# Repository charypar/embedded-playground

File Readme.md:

# Niche device firmware

## Flashing bootloader

Using a probe

```sh
make flash-bootloader
```

## Flashing firmware

For Spinny, for example:

With a probe:

```sh
make flash-spinny
```

Over USB

```sh
make upload-spinny
```

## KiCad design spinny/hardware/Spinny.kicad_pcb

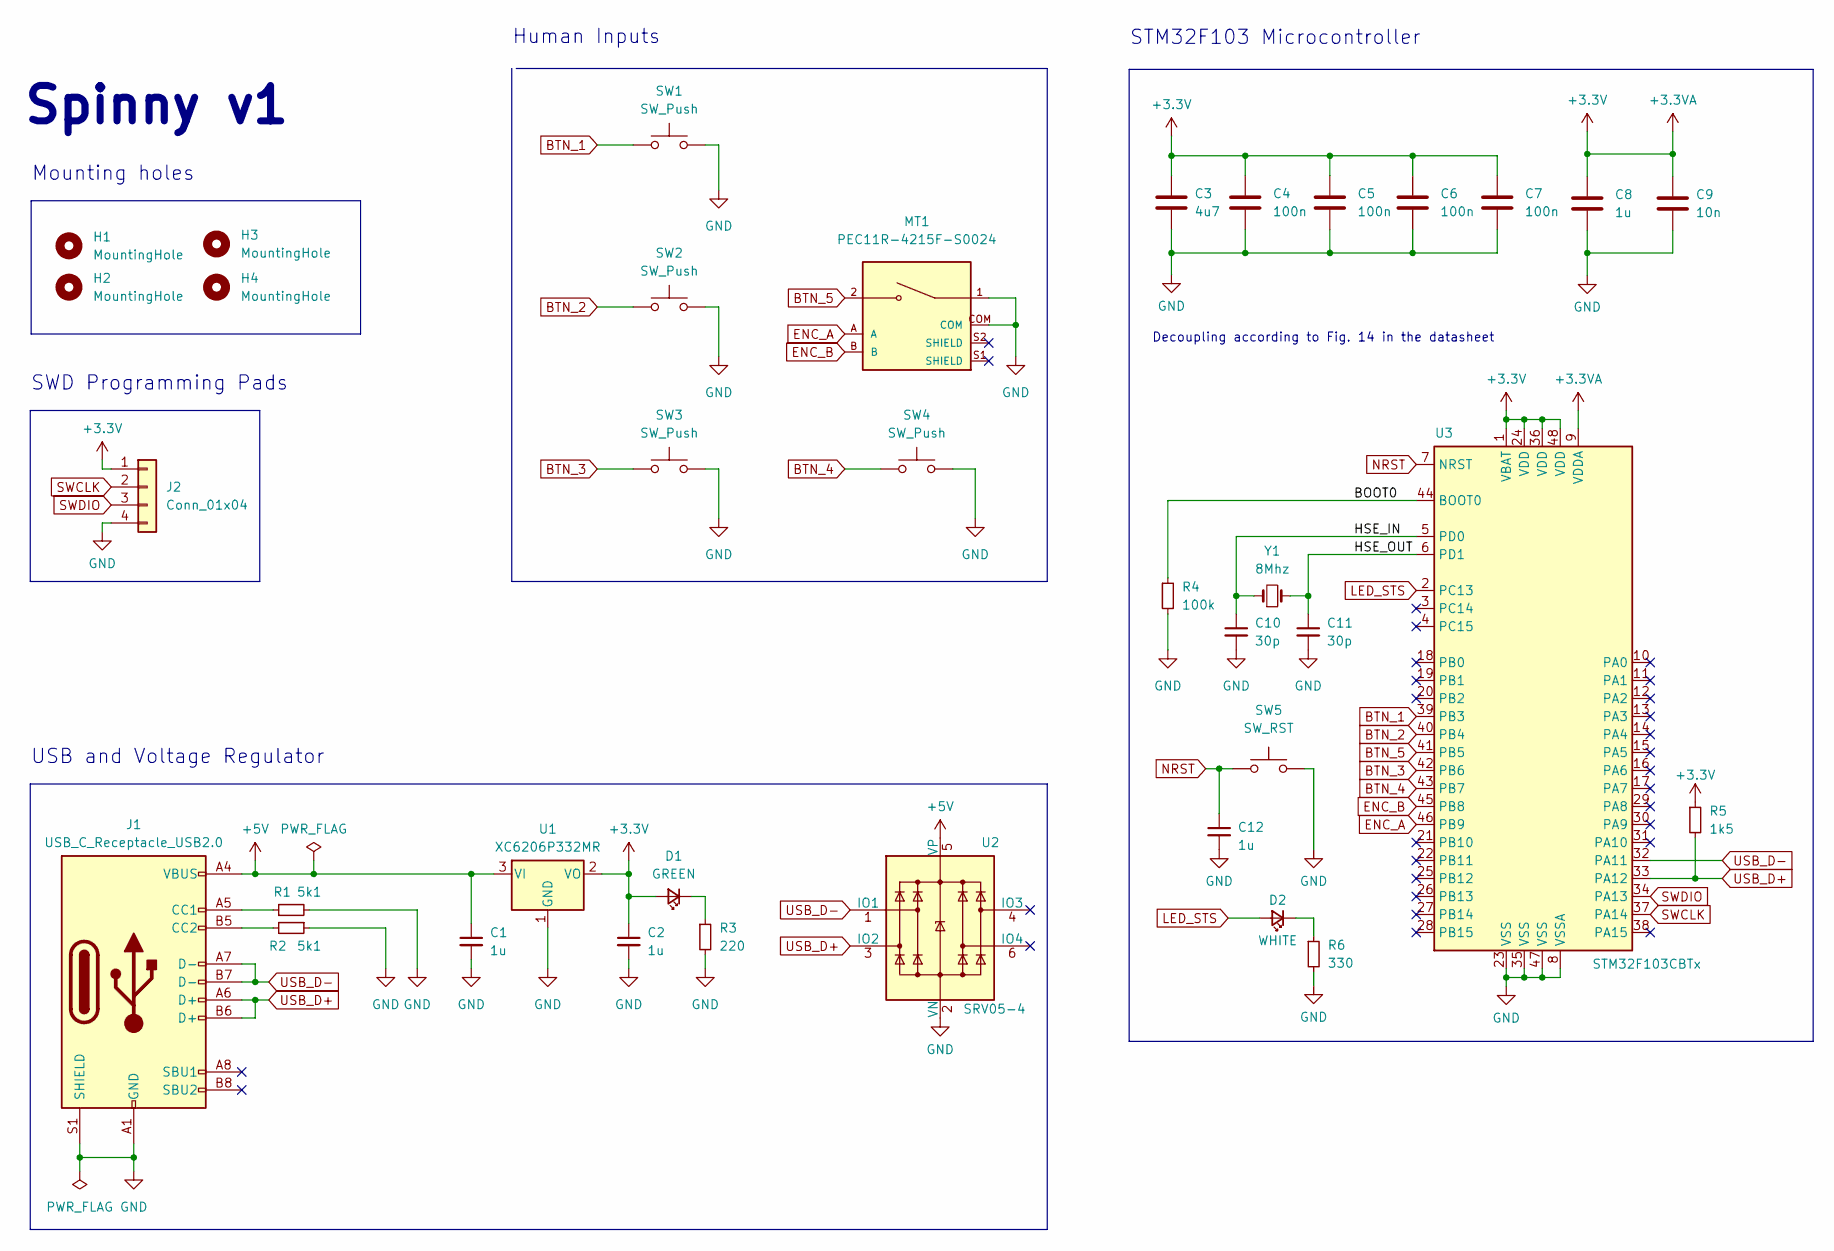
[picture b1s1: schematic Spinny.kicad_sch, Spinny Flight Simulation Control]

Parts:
C1, C2, C8, C12: 1u; C_0402_1005Metric; LCSC C52923
C3: 4u7; C_0603_1608Metric; LCSC C19666
C4, C5, C6, C7: 100n; C_0402_1005Metric; LCSC C1525
C9: 10n; C_0402_1005Metric; LCSC C15195
C10, C11: 30p; C_0402_1005Metric; LCSC C1570
D1: GREEN; LED_0603_1608Metric; LCSC C72043
D2: WHITE; LED_0603_1608Metric; LCSC C2290
H1, H2, H3, H4: MountingHole; MountingHole_3.2mm_M3
J1: USB_C_Receptacle_USB2.0; USB_C_Receptacle_HRO_TYPE-C-31-M-12; LCSC C709357
J2: Conn_01x04; PinHeader_1x04_P2.54mm_Vertical
MT1: PEC11R-4215F-S0024; XDCR_PEC11R-4215F-S0024; PARTREV Rev. 09/19
R1, R2: 5k1; R_0402_1005Metric; LCSC C25905
R3: 220; R_0402_1005Metric; LCSC C25091
R4: 100k; R_0402_1005Metric; LCSC C25741
R5: 1k5; R_0402_1005Metric; LCSC C25867
R6: 330; R_0402_1005Metric; LCSC C25104
SW1, SW2, SW3, SW4: SW_Push; SW_TS02-66-43-BK-100-LCR-D
SW5: SW_RST; SMD-SW-4_5.1x5.1x1.5; LCSC C318884
U1: XC6206P332MR; SOT-23; LCSC C5446
U2: SRV05-4; SOT-23-6; LCSC C85364
U3: STM32F103CBTx; LQFP-48_7x7mm_P0.5mm; LCSC C8304
Y1: 8Mhz; Crystal_SMD_5032-2Pin_5.0x3.2mm; LCSC C115962

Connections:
+5V: C1.1, J1.A4 (VBUS), J1.A9 (VBUS), J1.B4 (VBUS), J1.B9 (VBUS), U1.3 (VI), U2.5 (VP)
/BOOT0: R4.1, U3.44 (BOOT0)
/HSE_IN: C10.1, U3.5 (PD0), Y1.1
/HSE_OUT: C11.1, U3.6 (PD1), Y1.2
BTN_1: SW1.1, U3.39 (PB3)
BTN_2: SW2.1, U3.40 (PB4)
BTN_3: SW3.1, U3.42 (PB6)
BTN_4: SW4.1, U3.43 (PB7)
BTN_5: MT1.2, U3.41 (PB5)
ENC_A: MT1.A, U3.46 (PB9)
ENC_B: MT1.B, U3.45 (PB8)
GND: C1.2, C2.2, C3.2, C4.2, C5.2, C6.2, C7.2, C8.2, C9.2, C10.2, C11.2, C12.2, J1.A1 (GND), J1.A12 (GND), J1.B1 (GND), J1.B12 (GND), J1.S1 (SHIELD), J2.4, MT1.1, MT1.COM, R1.2, R2.1, R3.2, R4.2, R6.2, SW1.2, SW2.2, SW3.2, SW4.2, SW5.2, U1.1 (GND), U2.2 (VN), U3.8 (VSSA), U3.23 (VSS), U3.35 (VSS), U3.47 (VSS)
LED_STS: D2.2 (A), U3.2 (PC13)
NRST: C12.1, SW5.1, U3.7 (NRST)
unnamed: D1.1 (K), R3.1
unnamed: D2.1 (K), R6.1
unnamed: J1.A5 (CC1), R1.1
unnamed: J1.B5 (CC2), R2.2
SWCLK: J2.2, U3.37 (PA14)
SWDIO: J2.3, U3.34 (PA13)
USB_D+: J1.A6 (D+), J1.B6 (D+), R5.2, U2.3 (IO2), U3.33 (PA12)
USB_D-: J1.A7 (D-), J1.B7 (D-), U2.1 (IO1), U3.32 (PA11)

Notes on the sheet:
SWD Programming Pads
Decoupling according to Fig. 14 in the datasheet
Spinny v1
Human Inputs
STM32F103 Microcontroller
Mounting holes
USB and Voltage Regulator

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
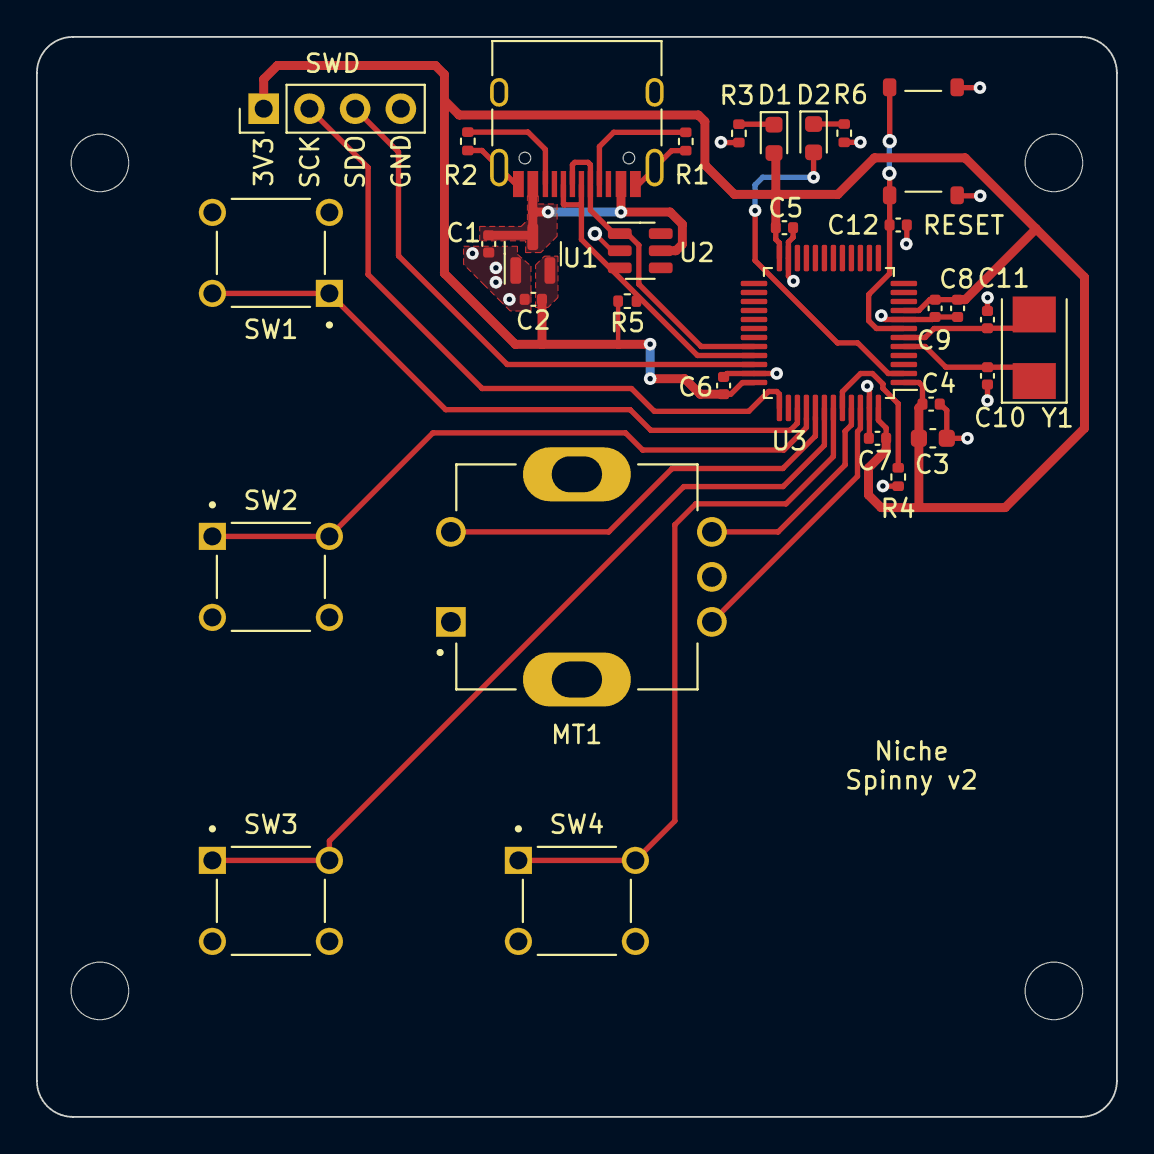
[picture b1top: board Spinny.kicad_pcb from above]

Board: 2 copper layers, 60.0 x 60.0 mm, 36 parts (0 on the bottom side), 23 nets.

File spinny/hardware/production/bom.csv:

Comment,Designator,Footprint,LCSC
1u,"C1,C2,C8,C12",Capacitor_SMD:C_0402_1005Metric,C52923
4u7,C3,Capacitor_SMD:C_0603_1608Metric,C19666
100n,"C4,C5,C6,C7",Capacitor_SMD:C_0402_1005Metric,C1525
10n,C9,Capacitor_SMD:C_0402_1005Metric,C15195
30p,"C10,C11",Capacitor_SMD:C_0402_1005Metric,C1570
GREEN,D1,LED_SMD:LED_0603_1608Metric,C72043
WHITE,D2,LED_SMD:LED_0603_1608Metric,C2290
USB_C_Receptacle_USB2.0,J1,Connector_USB:USB_C_Receptacle_HRO_TYPE-C-31-M-12,C709357
Conn_01x04,J2,Connector_PinHeader_2.54mm:PinHeader_1x04_P2.54mm_Vertical,
PEC11R-4215F-S0024,MT1,DigiKey:XDCR_PEC11R-4215F-S0024,
5k1,"R1,R2",Resistor_SMD:R_0402_1005Metric,C25905
220,R3,Resistor_SMD:R_0402_1005Metric,C25091
100k,R4,Resistor_SMD:R_0402_1005Metric,C25741
1k5,R5,Resistor_SMD:R_0402_1005Metric,C25867
330,R6,Resistor_SMD:R_0402_1005Metric,C25104
SW_Push,"SW1,SW2,SW3,SW4",DigiKey:SW_TS02-66-43-BK-100-LCR-D,
SW_RST,SW5,JLCPCB:SMD-SW-4_5.1x5.1x1.5,C318884
XC6206P332MR,U1,Package_TO_SOT_SMD:SOT-23,C5446
SRV05-4,U2,Package_TO_SOT_SMD:SOT-23-6,C85364
STM32F103C8T6,U3,Package_QFP:LQFP-48_7x7mm_P0.5mm,C8734
8Mhz,Y1,Crystal:Crystal_SMD_5032-2Pin_5.0x3.2mm,C115962

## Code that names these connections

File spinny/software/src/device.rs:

use hal::prelude::*;
use stm32f1xx_hal as hal;

use hal::pac;
use pac::{BKP, PWR, RCC, SCB};

use hal::gpio::gpiob::{PB3, PB4, PB5, PB6, PB7, PB8, PB9};
use hal::gpio::gpioc::PC13;
use hal::gpio::{GpioExt, Input, Output, PullUp, PushPull};
use hal::pac::Peripherals;
use hal::usb::{Peripheral, UsbBus};

use usb_device::class_prelude::UsbBusAllocator;

pub struct Device {
    pub bootloader: Bootloader,
    pub pb3: PB3<Input<PullUp>>,
    pub pb4: PB4<Input<PullUp>>,
    pub pb5: PB5<Input<PullUp>>,
    pub pb6: PB6<Input<PullUp>>,
    pub pb7: PB7<Input<PullUp>>,
    pub pb8: PB8<Input<PullUp>>,
    pub pb9: PB9<Input<PullUp>>,
    pub led: PC13<Output<PushPull>>,
    pub usb: UsbBusAllocator<UsbBus<Peripheral>>,
}

impl Device {
    pub fn new(device: Peripherals) -> Self {
        let rcc = device.RCC;
        let pwr = device.PWR;
        let flash = device.FLASH;
        let afio = device.AFIO;

        let bootloader = Bootloader::new(device.BKP, &rcc, &pwr);

        // Configure clocks
        let rcc = rcc.constrain();
        let mut acr = flash.constrain().acr;
        rcc.cfgr
            .use_hse(8.MHz()) // External crystal is on 8 Mhz
            .sysclk(72.MHz()) // Clock system on 72 Mhz, used also by USB, divided by 1.5 to 48 MHz
            .freeze(&mut acr);

        let mut gpioa = device.GPIOA.split();
        let mut gpiob = device.GPIOB.split();
        let mut gpioc = device.GPIOC.split();

        // Disable JTAG to allow access to PB3 and PB4
        let (_, pb3, pb4) = afio
            .constrain()
            .mapr
            .disable_jtag(gpioa.pa15, gpiob.pb3, gpiob.pb4);

        // Enable USB

        // FIXME why is this a thing again?
        // and do we need to sleep after?
        let mut usb_dp = gpioa.pa12.into_push_pull_output(&mut gpioa.crh);
        usb_dp.set_low();

        let usb = UsbBus::new(Peripheral {
            usb: device.USB,
            pin_dm: gpioa.pa11,
            pin_dp: usb_dp.into_floating_input(&mut gpioa.crh),
        });

        let mut led = gpioc.pc13.into_push_pull_output(&mut gpioc.crh);
        led.set_low();

        Device {
            pb3: pb3.into_pull_up_input(&mut gpiob.crl),
            pb4: pb4.into_pull_up_input(&mut gpiob.crl),
            pb5: gpiob.pb5.into_pull_up_input(&mut gpiob.crl),
            pb6: gpiob.pb6.into_pull_up_input(&mut gpiob.crl),
            pb7: gpiob.pb7.into_pull_up_input(&mut gpiob.crl),
            pb8: gpiob.pb8.into_pull_up_input(&mut gpiob.crh),
            pb9: gpiob.pb9.into_pull_up_input(&mut gpiob.crh),
            bootloader,
            led,
            usb,
        }
    }
}

// A convenient dapboot bootloader interface
pub struct Bootloader {
    bkp: BKP,
}

impl Bootloader {
    const RESET_TO_BOOTLOADER: u32 = 0x4F42;

    // Create a bootloader inteface and enable signaling
    pub fn new(bkp: BKP, rcc: &RCC, pwr: &PWR) -> Self {
        // From stm32 reference manual, pg 81:
        // 1. enable the power and backup interface clocks
        // 2. set the DBP bit in the Power control register

        rcc.apb1enr.write(|w| w.pwren().set_bit().bkpen().set_bit());
        pwr.cr.write(|w| w.dbp().set_bit());

        Self { bkp }
    }

    // Restart the device into bootloader
    pub fn reset(&self) {
        // from dapboot documentation/source code
        // https://github.com/devanlai/dapboot#switching-to-the-bootloader
        // https://github.com/devanlai/dapboot/blob/master/src/stm32f103/backup.c#L25
        //
        // 3. write the bootloader signal
        self.bkp.dr[0].write(|w| unsafe { w.bits(Self::RESET_TO_BOOTLOADER) });

        // check the write succeeded
        if self.bkp.dr[0].read().bits() == Self::RESET_TO_BOOTLOADER {
            SCB::sys_reset();
        }
    }
}

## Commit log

2022-01-16 Initial
2022-01-23 Port to Trinket M0 (ATSAMD21E)
2022-01-30 Blinky v2 with (broken) matrix wiring
2022-01-31 Switch from bit bang SPI to hardware SPI
2022-02-02 Send inputs over serial
2022-02-13 Switch to RTIC, add debouncing in the process
2022-02-14 Shuffle things about to make them easier to find
2022-02-18 Workign HID keyboard
2022-02-21 Add reading rotary as button presses, clean up a bit
2022-02-21 Remove arduino code
2022-02-21 Make the device a composite with Interface Association Descriptors
2022-02-23 Fix bug where writes into serial port break... everything
2022-02-27 Switch to HID Joystick
2022-03-06 Buffer encoder output and replay it at reliable rate
2022-03-08 Split code to device and cross-platform to allow unit tests on host
2022-03-08 Add tests for debouncing and holding
2022-03-08 Also report the rotary as a relative dial axis
2022-05-22 Remove cargo workspace, add Spinny device, add DAPlink probe debugging conifg
2022-05-24 Speed up input scanning and track real time for measuring how long things take
2022-07-10 Add Spinny hardware design
2022-07-11 Add production files
2022-07-11 Ignore KiCad backup files
2022-07-11 Update part numbers and automate Gerber, BOM and CPL files
2022-07-25 Adjust board to fit enclosure beter
2022-07-25 Move production files
2022-07-26 Add enclosure files
2022-08-07 Spinny v2: Fix wiring of tactile switches
2022-08-07 Port Spinny onto stm32 - basic blinking LED
2022-08-07 Small tweaks
2022-08-07 Spinny v2: fixes
2022-08-29 Enclosure v2
2022-08-29 Spinny V2 with stm32f104cbt6 instead of c8t6, because JLCPCB is random
2022-09-11 Add bootloader automation and USB only operation
2022-09-11 Spinny V2 schema file I forgot to commit
2022-10-09 Fix up for new laptop. This is not portable...
2022-10-09 Re-enable buttons, only send HID reports when new state is available
2022-10-15 Extract usb and bootloader signaling
2022-10-15 Make USB module portable
2022-10-15 Factor out stm32 specific peripheral setup
2022-10-15 Bound inputs
2022-10-15 Collect inputs into a panel
2022-10-15 Remove disused bootloader module file
2022-10-15 Remove stray comments
2022-10-31 Fix rotary reporting and add a slight velocity curve
